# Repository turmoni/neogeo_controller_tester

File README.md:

# neogeo_controller_tester

A simple board that tests the pins of a NeoGeo/Supergun-compatible DA15 controller. Ultimately this is a slightly fancy way of getting 5V through a bunch of LEDs, which will illuminate when the corresponding button is pressed.

I created this for my own use with building [my 9pin2supergun project](https://github.com/turmoni/9pin2supergun), as a simple visual way to check whether my hardware and code were working properly, but I can imagine it being useful to other people.

This is also a bit of a first step in figuring out how to share a KiCad project properly.

## Building one

The KiCad project is in this directory, and for convenience each push gets rendered to the `rendered` directory as a PDF of the schematics, and a set of gerber files. You *should* be able to use [the gerber archive](rendered/gbr.zip) to order boards directly, but for best results you should generate them yourself following your PCB fabricator's instructions (e.g. [for JLCPCB](https://jlcpcb.com/help/article/how-to-generate-gerber-and-drill-files-in-kicad-7)).

This board is designed to be pretty simple to put together, with the option to entirely use through-hole components if you are happy using USB type B for power, or a few surface mount ones if you want to use type C.

The BOM is largely up to your requirements; pretty much any normal LEDs will work, and the resistor value you choose is dependent on your LED and preferred brightness. I have put together [a list on DigiKey](https://www.digikey.co.uk/en/mylists/list/GHFYWIZHWM) for the parts I'm using, but there are still some options:

 * Omit the type C connector and 5.1k resistors if you only want to work with through-hole soldering
 * Omit the type B connector if you don't want it
 * The LED resistors can either be separate individual resistors of your chosen value, or SIP resistor arrays, whichever you prefer/can get your hands on. There should be no functional difference, I just found it tedious dealing with shaping, soldering, and snipping twelve individual resistors in the first revision of this board

## Using

There's not really much to it - plug it into a single power source (type B, type C, or, if it provides power (which it likely shouldn't), your controller), press buttons, see what lights up.

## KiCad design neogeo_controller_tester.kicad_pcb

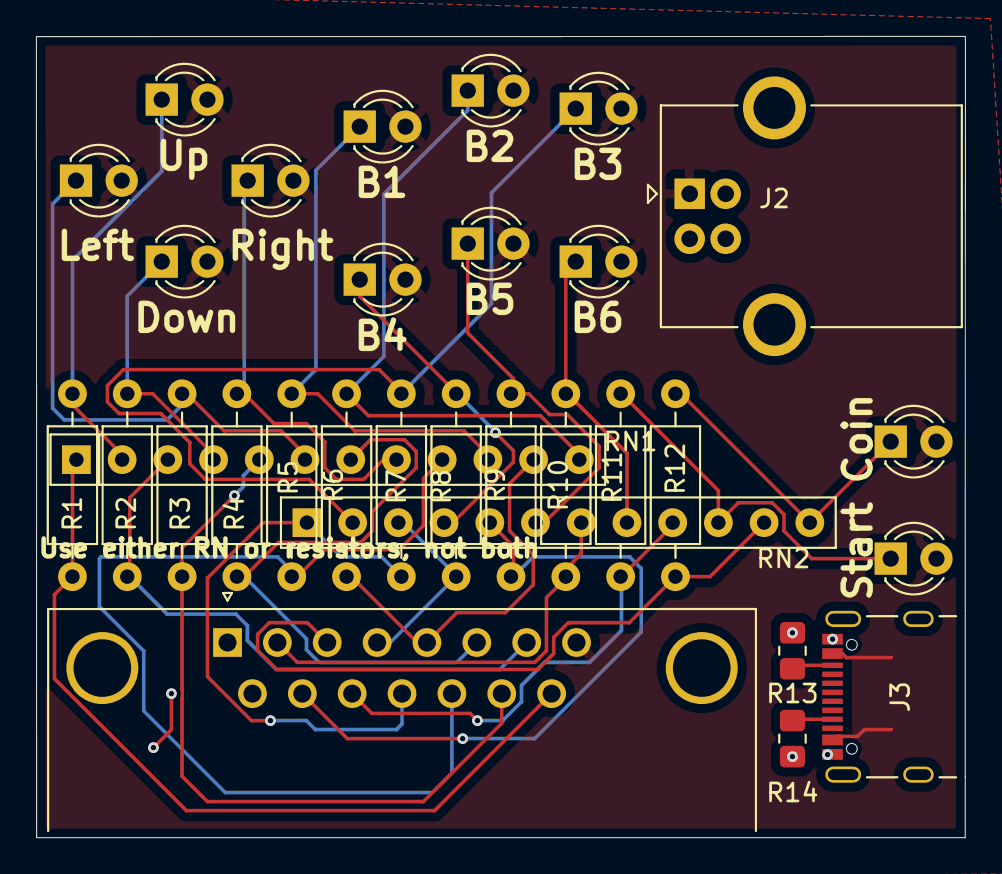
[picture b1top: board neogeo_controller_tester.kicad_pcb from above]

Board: 2 copper layers, 51.6 x 44.5 mm, 31 parts (0 on the bottom side), 28 nets.

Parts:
D1, D2, D3, D4, D5, D6, D7, D8, D9, D10, D11, D12: LED; LED_D3.0mm
J1: DA15_Plug; DSUB-15_Male_Horizontal_P2.77x2.84mm_EdgePinOffset7.70mm_Ho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
J2: USB_B; USB_B_OST_USB-B1HSxx_Horizontal
J3: UJ20-C-H-C-4-SMT-TR; CUI_UJ20-C-H-C-4-SMT-TR
R1, R2, R3, R4, R5, R6, R7, R8, R9, R10, R11, R12: 150R; R_Axial_DIN0207_L6.3mm_D2.5mm_P10.16mm_Horizontal
R13, R14: 5.1k; R_0805_2012Metric_Pad1.20x1.40mm_HandSolder
RN1, RN2: R_Pack06_SIP; R_Array_SIP12

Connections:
/Button 1: J1.13, R5.1, RN1.9 (R5.1)
/Button 1 LED: D5.1 (K), R5.2, RN1.10 (R5.2)
/Button 2: J1.5, R6.1, RN1.11 (R6.1)
/Button 2 LED: D6.1 (K), R6.2, RN1.12 (R6.2)
/Button 3: J1.12, R7.1, RN2.1 (R1.1)
/Button 3 LED: D7.1 (K), R7.2, RN2.2 (R1.2)
/Button 4: J1.4, R8.1, RN2.3 (R2.1)
/Button 4 LED: D8.1 (K), R8.2, RN2.4 (R2.2)
/Button 5: J1.10, R9.1, RN2.5 (R3.1)
/Button 5 LED: D9.1 (K), R9.2, RN2.6 (R3.2)
/Button 6: J1.2, R10.1, RN2.7 (R4.1)
/Button 6 LED: D10.1 (K), R10.2, RN2.8 (R4.2)
/Coin: J1.3, R12.1, RN2.11 (R6.1)
/Coin LED: D12.1 (K), R12.2, RN2.12 (R6.2)
/Down: J1.7, R2.1, RN1.3 (R2.1)
/Down LED: D2.1 (K), R2.2, RN1.4 (R2.2)
/Left: J1.14, R3.1, RN1.5 (R3.1)
/Left LED: D3.1 (K), R3.2, RN1.6 (R3.2)
/Right: J1.6, R4.1, RN1.7 (R4.1)
/Right LED: D4.1 (K), R4.2, RN1.8 (R4.2)
/Start: J1.11 (P111), R11.1, RN2.9 (R5.1)
/Start LED: D11.1 (K), R11.2, RN2.10 (R5.2)
/Up: J1.15, R1.1, RN1.1 (R1.1)
/Up LED: D1.1 (K), R1.2, RN1.2 (R1.2)
GND: J1.1, J2.4 (GND), J2.5 (Shield), J3.A1_B12 (GND), J3.A12_B1 (GND__1), J3.SH1 (SHIELD), J3.SH2 (SHIELD__1), J3.SH3 (SHIELD__2), J3.SH4 (SHIELD__3), R13.1, R14.2
unnamed: J3.A5 (CC1), R14.1
unnamed: J3.B5 (CC2), R13.2
VBUS: D1.2 (A), D2.2 (A), D3.2 (A), D4.2 (A), D5.2 (A), D6.2 (A), D7.2 (A), D8.2 (A), D9.2 (A), D10.2 (A), D11.2 (A), D12.2 (A), J1.8, J2.1 (VBUS), J3.A4_B9 (VBUS), J3.A9_B4 (VBUS__1)

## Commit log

2024-11-01 Add PCB files
2024-11-01 Add a probably broken workflow that just attempts to render a PDF
2024-11-01 Try changing the path, which probably won't fix anything
2024-11-02 Change action, tested locally
2024-11-02 Add generated files to repo
2024-11-02 Fix version of download artifact
2024-11-02 Render schematics and gerbers
2024-11-02 Update README with more info
2024-11-02 Tidy up schematic
2024-11-03 Add CERN-OHL-P-2.0 licence
2024-11-03 Add .gitignore for KiCad files
2024-11-03 Only kick off render job if KiCad files have changed, rename from generate_pdfs
2024-11-17 Add a photo to the README
